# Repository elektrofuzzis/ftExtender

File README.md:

# ftExtender

*** english text below ***

Der I²C-Bus am TX(T) ist universell. Es lassen sich Sensoren und Aktoren für alle Anwendungsfälle anschließen und auch der ftDuino kann als preiswertes Erweiterungsboard am TX(T) angeschlossen werden. Der hier vorgestellte ftExtender löst die immer wiederkehrenden Themen
Versorgungspannung, Logikspannung und der Anschluss mehrerer Devices, so dass für den Anschluß von I²C-Geräten nur noch das passende
Kabel benötigt wird.

Das Projekt kann ebenfalls in Arduino und Raspberry Pi Projekten eingesetzt werden.

Im wiki https://github.com/elektrofuzzis/ftExtender/wiki sind Benutzung und Nachbau des ftExtender beschrieben. Der ftExtender ist als fertiges Gerät verfügbar und kann hier bestellt werden: https://gundermann-software.de/shop

Der ftExtender ist ein Community-Projekt von www.ftcommunity.de.

------------------------------------------------------------------------------------------------------------------------------------------

Using the build in I²C-interface of fischertechnik TX and TXT controllers, you could connect all types of I²C devices. You could connect a ftDuino and us it as a simple I/O extension in RoboPro, too. But if you want to use a I²C device, you need to discuss logic levels and a power supply, first. This project solves these problems and you just need some cables to connect your devices.

You could use the ftExtender in your Arduino or Raspberry Pi projects, too.

The wiki https://github.com/elektrofuzzis/ftExtender/wiki describes usage and reprodution of the ftExtender. The ftExtender is available as a ready-made system, too. Please visit: https://gundermann-software.de/shop

This is a community project of www.ftcommunity.de.

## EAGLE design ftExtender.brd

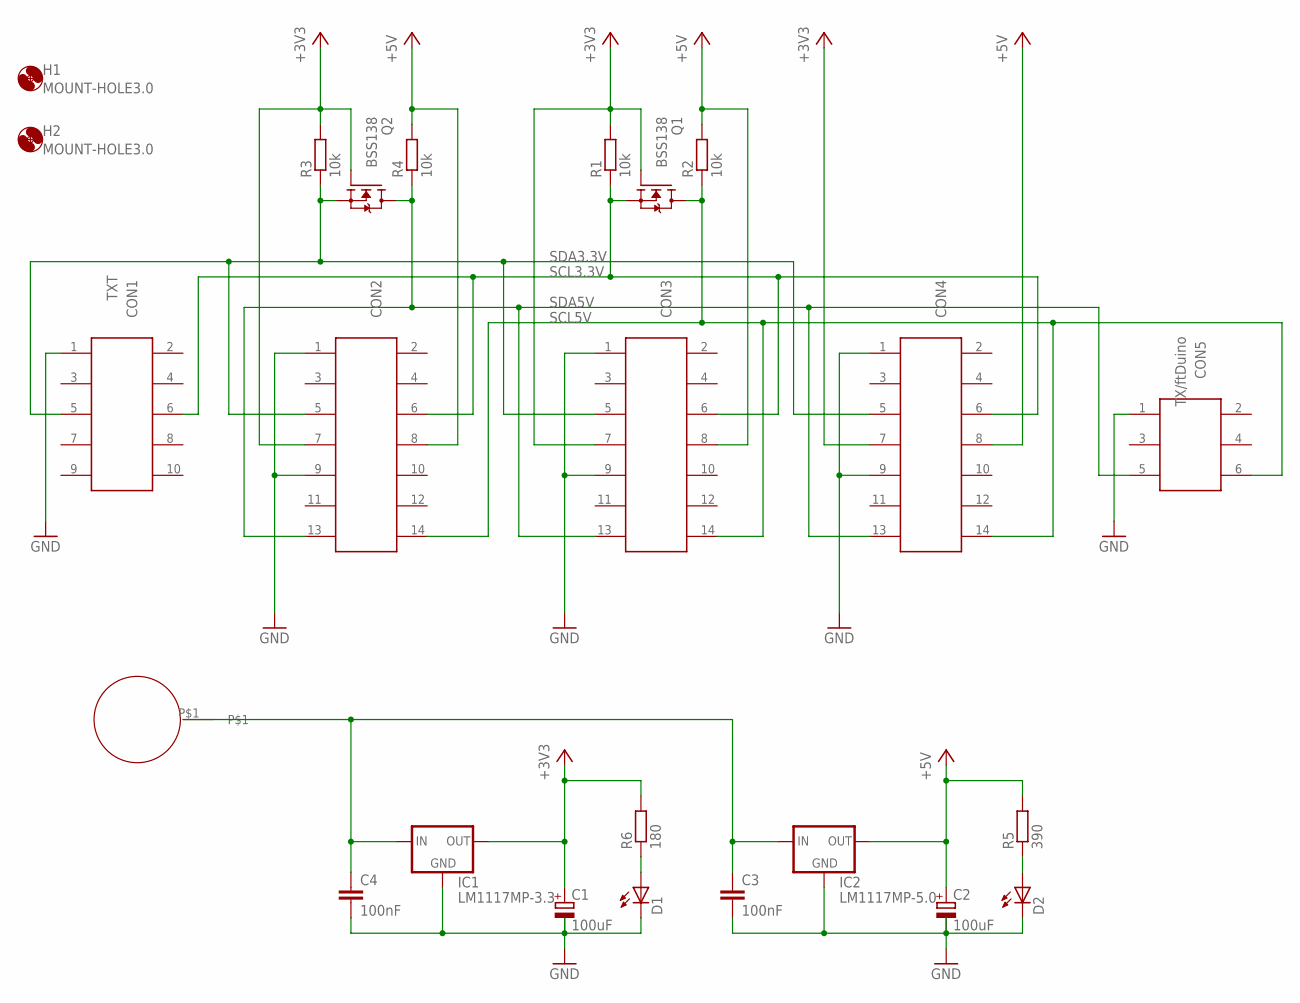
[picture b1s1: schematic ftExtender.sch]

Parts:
+9V: BUNDHUELSE
C1, C2: 100uF; CT3528
C3, C4: 100nF; C0603K
CON1: TXT; 612X1020621
CON2, CON3, CON4: 612X1420621
CON5: TX/ftDuino; SMTHEADER06
D1, D2: LEDCHIP-LED0805; CHIP-LED0805
H1, H2: MOUNT-HOLE3.0; 3,0
IC1: LM1117MP-3.3; SOT223
IC2: LM1117MP-5.0; SOT223
Q1, Q2: BSS138; SOT23
R1, R2, R3, R4: 10k; R0603
R5: 390; R0603
R6: 180; R0603

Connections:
+3V3: C1.- (+), CON2.7, CON3.7, CON4.7, IC1.2 (OUT), IC1.4 (OUT), Q1.1 (G), Q2.1 (G), R1.2, R3.2, R6.2
+5V: C2.- (+), CON2.8, CON3.8, CON4.8, IC2.2 (OUT), IC2.4 (OUT), R2.2, R4.2, R5.2
+9V: +9V.P$1, C3.1, C4.1, IC1.3 (IN), IC2.3 (IN)
GND: C1.+ (-), C2.+ (-), C3.2, C4.2, CON1.1, CON2.1, CON2.9, CON3.1, CON3.9, CON4.1, CON4.9, CON5.1, D1.C, D2.C, IC1.1 (GND), IC2.1 (GND)
unnamed: D2.A, R5.1
unnamed: D1.A, R6.1
SCL3.3V: CON1.6, CON2.6, CON3.6, CON4.6, Q1.2 (S), R1.1
SCL5V: CON2.14, CON3.14, CON4.14, CON5.6, Q1.3 (D), R2.1
SDA3.3V: CON1.5, CON2.5, CON3.5, CON4.5, Q2.2 (S), R3.1
SDA5V: CON2.13, CON3.13, CON4.13, CON5.5, Q2.3 (D), R4.1

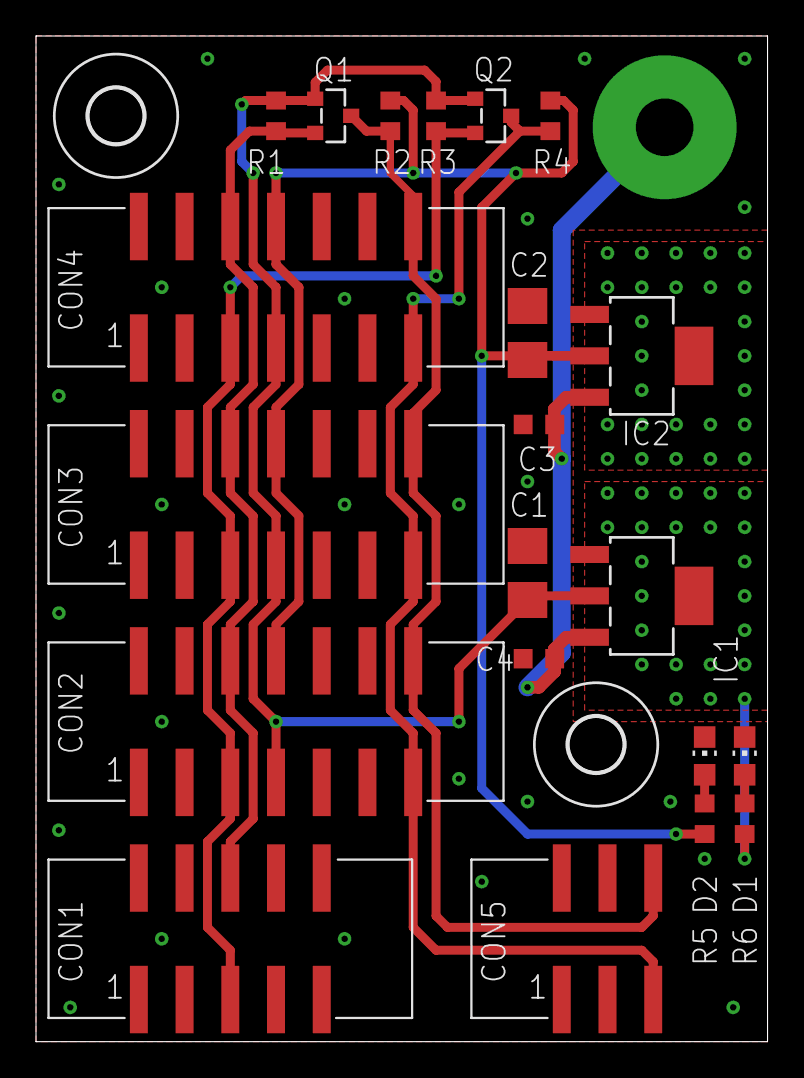
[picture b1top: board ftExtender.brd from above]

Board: 2 copper layers, 40.6 x 55.9 mm, 24 parts (0 on the bottom side), 10 nets.

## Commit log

2018-05-04 initial version
2018-05-05 Schaltplan als PDF
2018-06-19 Refactoring
2018-06-23 Add files via upload
    erste Fassung zum allgemeinen Review
2018-06-24 stl added
2018-06-26 Delete Handbuch_ft-Extender.pdf
    rework
2018-06-26 Add files via upload
    Handbuch zum ft-Extender

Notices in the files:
parts and their libraries:
Wire-to-Board: Copyright: Würth Elektronik
